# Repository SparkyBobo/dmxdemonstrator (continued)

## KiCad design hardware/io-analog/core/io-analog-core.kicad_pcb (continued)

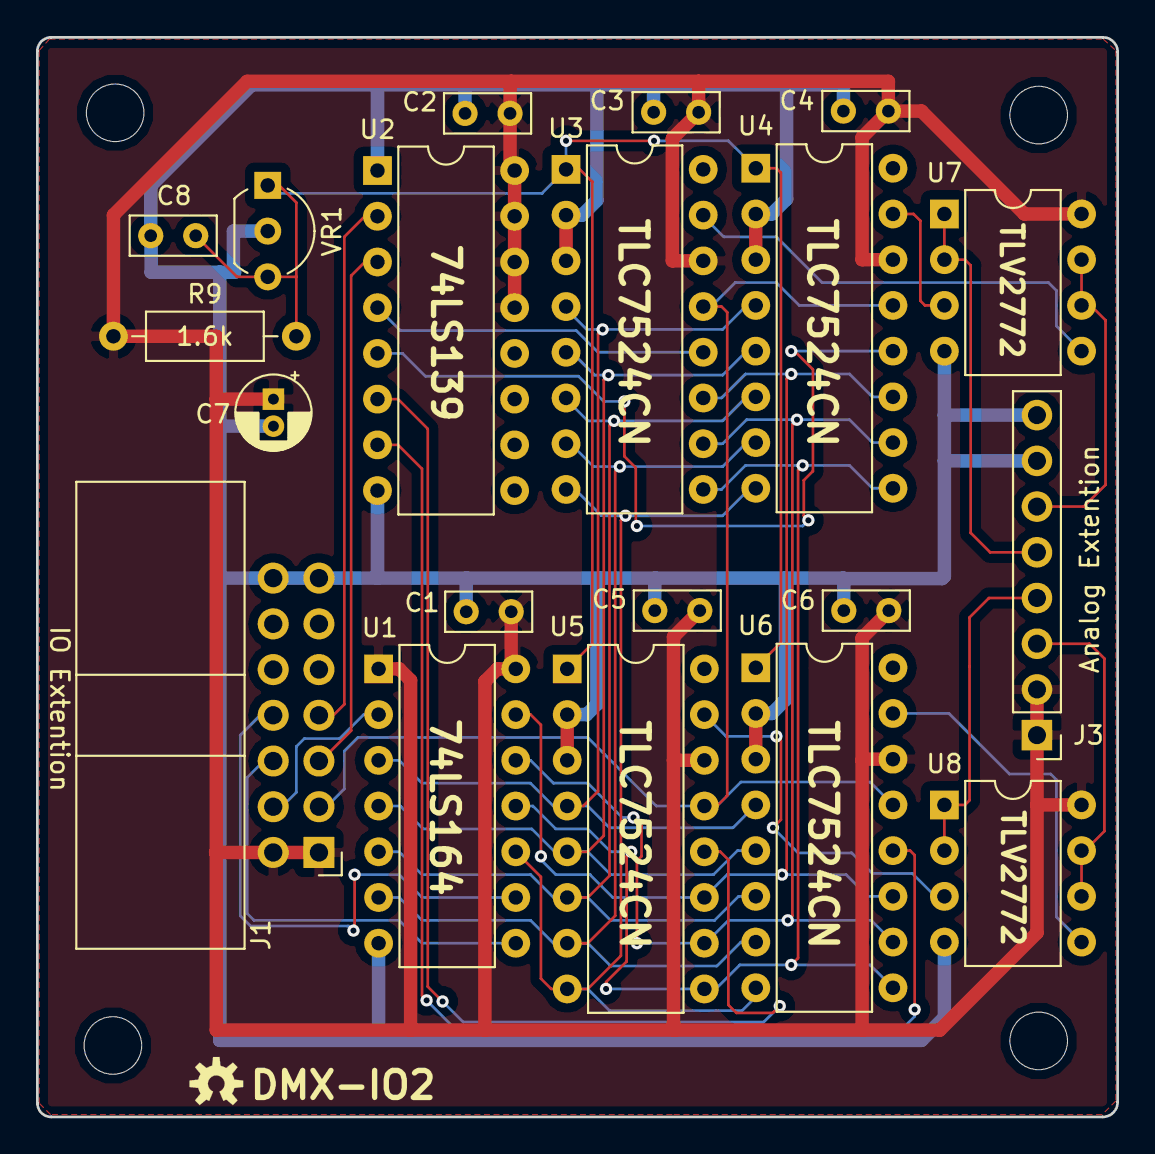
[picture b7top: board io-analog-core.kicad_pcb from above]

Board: 2 copper layers, 60.0 x 60.0 mm, 24 parts (0 on the bottom side), 29 nets.

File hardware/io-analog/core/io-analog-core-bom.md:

# Bill Of Materials (BOM)

## Schematic

**Filename:** E:\OpenSource\dmxdemonstrator\hardware\io-analog\core\io-analog-core.sch

**Date Modified:** 8/20/2023 10:52:49 PM

**Kicad Version:** Eeschema (5.0.0)

**Component Count:** 24

## Parts

Reference|Quantity|Value|Part|Datasheet|Vendor(s)
---------|--------|-----|----|---------|------
C1, C2, C3, C4, C5, C6, C8|7|0.1uF|Decoupling Capacitor|~|[Mouser 80-C320C104K5R7301](https://www.mouser.com/ProductDetail/KEMET/C320C104K5R5TA730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, [Newark 13K6284](https://www.newark.com/kemet/c315c104m5u5ta/capacitor-mlcc-z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, [Sparkfun COM-08375](https://www.sparkfun.com/products/8375), [Adafruit 753](https://www.adafruit.com/product/753)
C7|1|10uF|Filter Capacitor|~|[Digikey P10425CT-ND](https://www.digikey.com/en/products/detail/panasonic-electro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, [Mouser 667-ECA-1HM100I](https://www.mouser.com/ProductDetail/Panasonic/ECA-1HM100I), [Newark ECA-1HM100I](), [Sparkfun COM-00523](https://www.sparkfun.com/products/523), [Adafruit 2195](https://www.adafruit.com/product/2195)
J1|1|IO Extension||[Data Sheet](https://www.we-online.com/components/products/datasheet/6120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|[Digikey 732-5407-ND](https://www.digikey.com/en/products/detail/würth-elektronik/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, [Mouser 710-61201421721](https://www.mouser.com/ProductDetail/Wurth-Elektronik/612014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, [Newark 75AJ1395](https://www.newark.com/wurth-elektronik/612014235221/conn-r-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
J3|1|Analog Extension|Header - 8 Pin|~|[Mouser 992-8FX1-254MM](https://www.mouser.com/ProductDetail/Gravitech/8Fx1-254mm?qs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, [Sparkfun PRT-11895](https://www.sparkfun.com/products/11895)
R9|1|1.6k||~|[Digikey 1.6KQBK-ND](https://www.digikey.com/en/products/detail/yageo/CFR-25JB-52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, [Mouser 603-CFR-25JB-52-1K6](https://www.mouser.com/ProductDetail/YAGEO/CFR-25JB-52-1K6?q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, [Newark 59K8662](https://www.newark.com/multicomp-pro/mcmf0w4ff1601a50/metal-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
U1|1|74LS164|8-Bit Parallel-Out Serial Shift Register|[Data Sheet](http://www.ti.com/general/docs/suppproductinfo.tsp?distId=10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|[Digikey 296-1647-5-ND](https://www.digikey.com/en/products/detail/texas-instruments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, [Mouser 595-SN74LS164N](https://www.mouser.com/ProductDetail/Texas-Instruments/SN74L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
U2|1|74LS139|Dual 2-line to 4-line decoders|[Data Sheet](https://www.ti.com/lit/gpn/sn74ls139a)|[Digikey 296-1640-5-ND](https://www.digikey.com/en/products/detail/texas-instruments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, [Mouser 595-SN74LS139AN](https://www.mouser.com/ProductDetail/Texas-Instruments/SN74L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
U3, U4, U5, U6|4|TLC7524CN|8-bit Multiplying Digital to Analog Converter|[Data Sheet](https://www.ti.com/general/docs/suppproductinfo.tsp?distId=1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|[Digikey 296-1868-5-ND](https://www.digikey.com/en/products/detail/texas-instruments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, [Mouser 595-TLC7524CN](https://www.mouser.com/ProductDetail/Texas-Instruments/TLC75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
U7, U8|2|TLV2772|Rail-to-Rail Operational Amplifier|[Data Sheet](https://www.ti.com/lit/ds/slos209g/slos209g.pdf)|[Digikey 296-7592-5-ND](https://www.digikey.com/en/products/detail/texas-instruments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, [Mouser TLV2772CP](https://www.mouser.com/ProductDetail/Texas-Instruments/TLV27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
VR1|1|TL1431|Precision Voltage Reference|[Data Sheet](https://www.ti.com/lit/gpn/TL1431)|[Digikey 296-10130-5-ND](https://www.digikey.com/products/detail/texas-instruments/TL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, [Mouser 595-TL1431CLPR](https://www.mouser.com/ProductDetail/Texas-Instruments/TL143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
